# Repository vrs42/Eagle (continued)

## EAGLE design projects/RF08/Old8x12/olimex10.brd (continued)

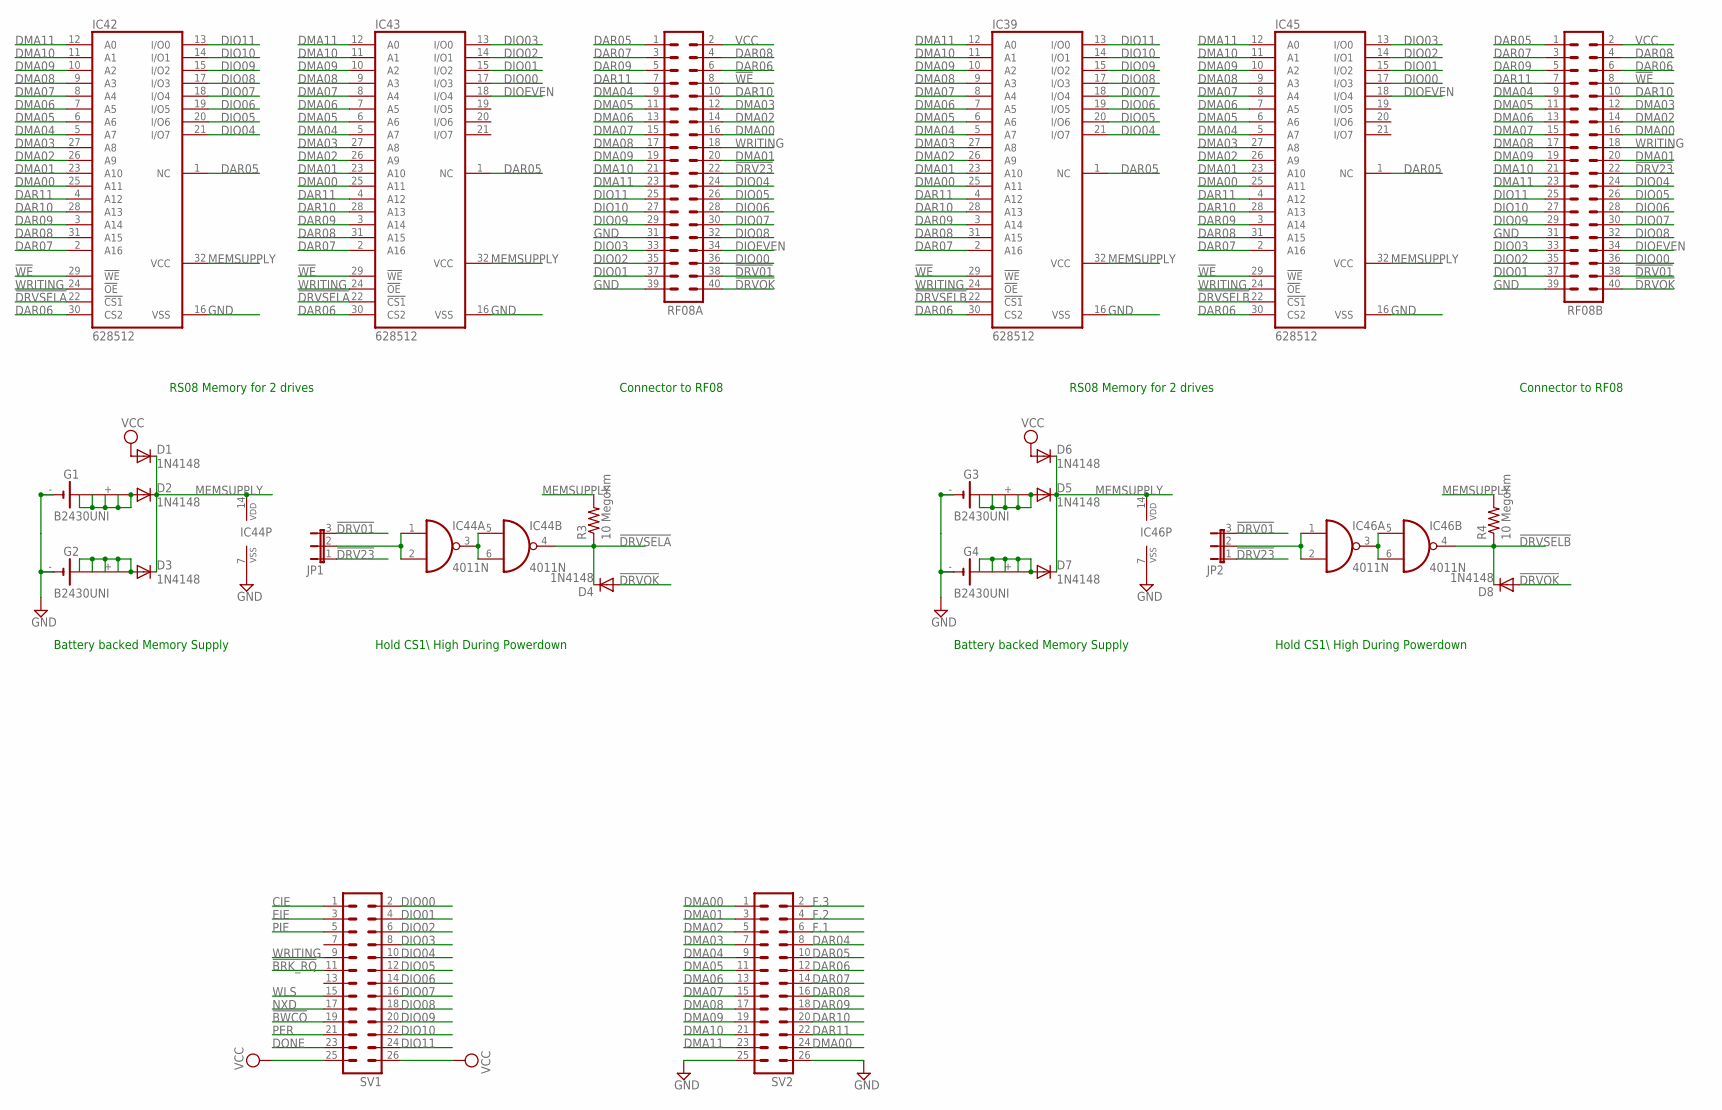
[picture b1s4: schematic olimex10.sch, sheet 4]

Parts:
D1, D2, D3, D4, D5, D6, D7, D8: 1N4148; DO35-10
G1, G2, G3, G4: B2430UNI
IC39, IC42, IC43, IC45: 628512; DIL32
IC44, IC46: 4011N; DIL14
JP1, JP2: JP2E; JP2
R3, R4: 10 Megohm; 0207/10
RF08A, RF08B: MA20-2
SV1, SV2: MA13-2

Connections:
!BRK_RQ: SV1.11; also elsewhere on the board
!BWCO: SV1.19; also elsewhere on the board
!DRV01: JP1.3, JP2.3, RF08A.38, RF08B.38; also elsewhere on the board
!DRV23: JP1.1, JP2.1, RF08A.22, RF08B.22; also elsewhere on the board
!DRVOK: D4.A, D8.A, RF08A.40, RF08B.40; also elsewhere on the board
!DRVSELA: D4.C, IC42.22 (!CS1), IC43.22 (!CS1), IC44.4 (O), R3.1
!DRVSELB: D8.C, IC39.22 (!CS1), IC45.22 (!CS1), IC46.4 (O), R4.1
!WE: IC39.29 (!WE), IC42.29 (!WE), IC43.29 (!WE), IC45.29 (!WE), RF08A.8, RF08B.8; also elsewhere on the board
CIE: SV1.1; also elsewhere on the board
DAR04: SV2.8; also elsewhere on the board
DAR05: IC39.1 (NC), IC42.1 (NC), IC43.1 (NC), IC45.1 (NC), RF08A.1, RF08B.1, SV2.10; also elsewhere on the board
DAR06: IC39.30 (CS2), IC42.30 (CS2), IC43.30 (CS2), IC45.30 (CS2), RF08A.6, RF08B.6, SV2.12; also elsewhere on the board
DAR07: IC39.2 (A16), IC42.2 (A16), IC43.2 (A16), IC45.2 (A16), RF08A.3, RF08B.3, SV2.14; also elsewhere on the board
DAR08: IC39.31 (A15), IC42.31 (A15), IC43.31 (A15), IC45.31 (A15), RF08A.4, RF08B.4, SV2.16; also elsewhere on the board
DAR09: IC39.3 (A14), IC42.3 (A14), IC43.3 (A14), IC45.3 (A14), RF08A.5, RF08B.5, SV2.18; also elsewhere on the board
DAR10: IC39.28 (A13), IC42.28 (A13), IC43.28 (A13), IC45.28 (A13), RF08A.10, RF08B.10, SV2.20; also elsewhere on the board
DAR11: IC39.4 (A12), IC42.4 (A12), IC43.4 (A12), IC45.4 (A12), RF08A.7, RF08B.7, SV2.22; also elsewhere on the board
DIO00: IC43.17 (I/O3), IC45.17 (I/O3), RF08A.36, RF08B.36, SV1.2; also elsewhere on the board
DIO01: IC43.15 (I/O2), IC45.15 (I/O2), RF08A.37, RF08B.37, SV1.4; also elsewhere on the board
DIO02: IC43.14 (I/O1), IC45.14 (I/O1), RF08A.35, RF08B.35, SV1.6; also elsewhere on the board
DIO03: IC43.13 (I/O0), IC45.13 (I/O0), RF08A.33, RF08B.33, SV1.8; also elsewhere on the board
DIO04: IC39.21 (I/O7), IC42.21 (I/O7), RF08A.24, RF08B.24, SV1.10; also elsewhere on the board
DIO05: IC39.20 (I/O6), IC42.20 (I/O6), RF08A.26, RF08B.26, SV1.12; also elsewhere on the board
DIO06: IC39.19 (I/O5), IC42.19 (I/O5), RF08A.28, RF08B.28, SV1.14; also elsewhere on the board
DIO07: IC39.18 (I/O4), IC42.18 (I/O4), RF08A.30, RF08B.30, SV1.16; also elsewhere on the board
DIO08: IC39.17 (I/O3), IC42.17 (I/O3), RF08A.32, RF08B.32, SV1.18; also elsewhere on the board
DIO09: IC39.15 (I/O2), IC42.15 (I/O2), RF08A.29, RF08B.29, SV1.20; also elsewhere on the board
DIO10: IC39.14 (I/O1), IC42.14 (I/O1), RF08A.27, RF08B.27, SV1.22; also elsewhere on the board
DIO11: IC39.13 (I/O0), IC42.13 (I/O0), RF08A.25, RF08B.25, SV1.24; also elsewhere on the board
DIOEVEN: IC43.18 (I/O4), IC45.18 (I/O4), RF08A.34, RF08B.34; also elsewhere on the board
DMA00: IC39.25 (A11), IC42.25 (A11), IC43.25 (A11), IC45.25 (A11), RF08A.16, RF08B.16, SV2.1, SV2.24; also elsewhere on the board
DMA01: IC39.23 (A10), IC42.23 (A10), IC43.23 (A10), IC45.23 (A10), RF08A.20, RF08B.20, SV2.3; also elsewhere on the board
DMA02: IC39.26 (A9), IC42.26 (A9), IC43.26 (A9), IC45.26 (A9), RF08A.14, RF08B.14, SV2.5; also elsewhere on the board
DMA03: IC39.27 (A8), IC42.27 (A8), IC43.27 (A8), IC45.27 (A8), RF08A.12, RF08B.12, SV2.7; also elsewhere on the board
DMA04: IC39.5 (A7), IC42.5 (A7), IC43.5 (A7), IC45.5 (A7), RF08A.9, RF08B.9, SV2.9; also elsewhere on the board
DMA05: IC39.6 (A6), IC42.6 (A6), IC43.6 (A6), IC45.6 (A6), RF08A.11, RF08B.11, SV2.11; also elsewhere on the board
DMA06: IC39.7 (A5), IC42.7 (A5), IC43.7 (A5), IC45.7 (A5), RF08A.13, RF08B.13, SV2.13; also elsewhere on the board
DMA07: IC39.8 (A4), IC42.8 (A4), IC43.8 (A4), IC45.8 (A4), RF08A.15, RF08B.15, SV2.15; also elsewhere on the board
DMA08: IC39.9 (A3), IC42.9 (A3), IC43.9 (A3), IC45.9 (A3), RF08A.17, RF08B.17, SV2.17; also elsewhere on the board
DMA09: IC39.10 (A2), IC42.10 (A2), IC43.10 (A2), IC45.10 (A2), RF08A.19, RF08B.19, SV2.19; also elsewhere on the board
DMA10: IC39.11 (A1), IC42.11 (A1), IC43.11 (A1), IC45.11 (A1), RF08A.21, RF08B.21, SV2.21; also elsewhere on the board
DMA11: IC39.12 (A0), IC42.12 (A0), IC43.12 (A0), IC45.12 (A0), RF08A.23, RF08B.23, SV2.23; also elsewhere on the board
DONE: SV1.23; also elsewhere on the board
EIE: SV1.3; also elsewhere on the board
F.1: SV2.6; also elsewhere on the board
F.2: SV2.4; also elsewhere on the board
F.3: SV2.2; also elsewhere on the board
GND: G1.-, G1.-@1 (-), G2.-, G2.-@1 (-), G3.-, G3.-@1 (-), G4.-, G4.-@1 (-), IC39.16 (VSS), IC42.16 (VSS), IC43.16 (VSS), IC44.7 (VSS), IC45.16 (VSS), IC46.7 (VSS), RF08A.31, RF08A.39, RF08B.31, RF08B.39, SV2.25, SV2.26; also elsewhere on the board
MEMSUPPLY: D1.C, D2.C, D3.C, D5.C, D6.C, D7.C, IC39.32 (VCC), IC42.32 (VCC), IC43.32 (VCC), IC44.14 (VDD), IC45.32 (VCC), IC46.14 (VDD), R3.2, R4.2
unnamed: IC44.3 (O), IC44.5 (I0), IC44.6 (I1)
unnamed: IC44.1 (I0), IC44.2 (I1), JP1.2
unnamed: D7.A, G4.+, G4.+@1 (+), G4.+@2 (+), G4.+@3 (+), G4.+@4 (+)
unnamed: IC46.3 (O), IC46.5 (I0), IC46.6 (I1)
unnamed: IC46.1 (I0), IC46.2 (I1), JP2.2
unnamed: D5.A, G3.+, G3.+@1 (+), G3.+@2 (+), G3.+@3 (+), G3.+@4 (+)
unnamed: D3.A, G2.+, G2.+@1 (+), G2.+@2 (+), G2.+@3 (+), G2.+@4 (+)
unnamed: D2.A, G1.+, G1.+@1 (+), G1.+@2 (+), G1.+@3 (+), G1.+@4 (+)
NXD: SV1.17; also elsewhere on the board
PER: SV1.21; also elsewhere on the board
PIE: SV1.5; also elsewhere on the board
VCC: D1.A, D6.A, RF08A.2, RF08B.2, SV1.25, SV1.26; also elsewhere on the board
WLS: SV1.15; also elsewhere on the board
WRITING: IC39.24 (!OE), IC42.24 (!OE), IC43.24 (!OE), IC45.24 (!OE), RF08A.18, RF08B.18, SV1.9; also elsewhere on the board

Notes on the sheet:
Hold CS1\\ High During Powerdown
Battery backed Memory Supply
RS08 Memory for 2 drives
Connector to RF08

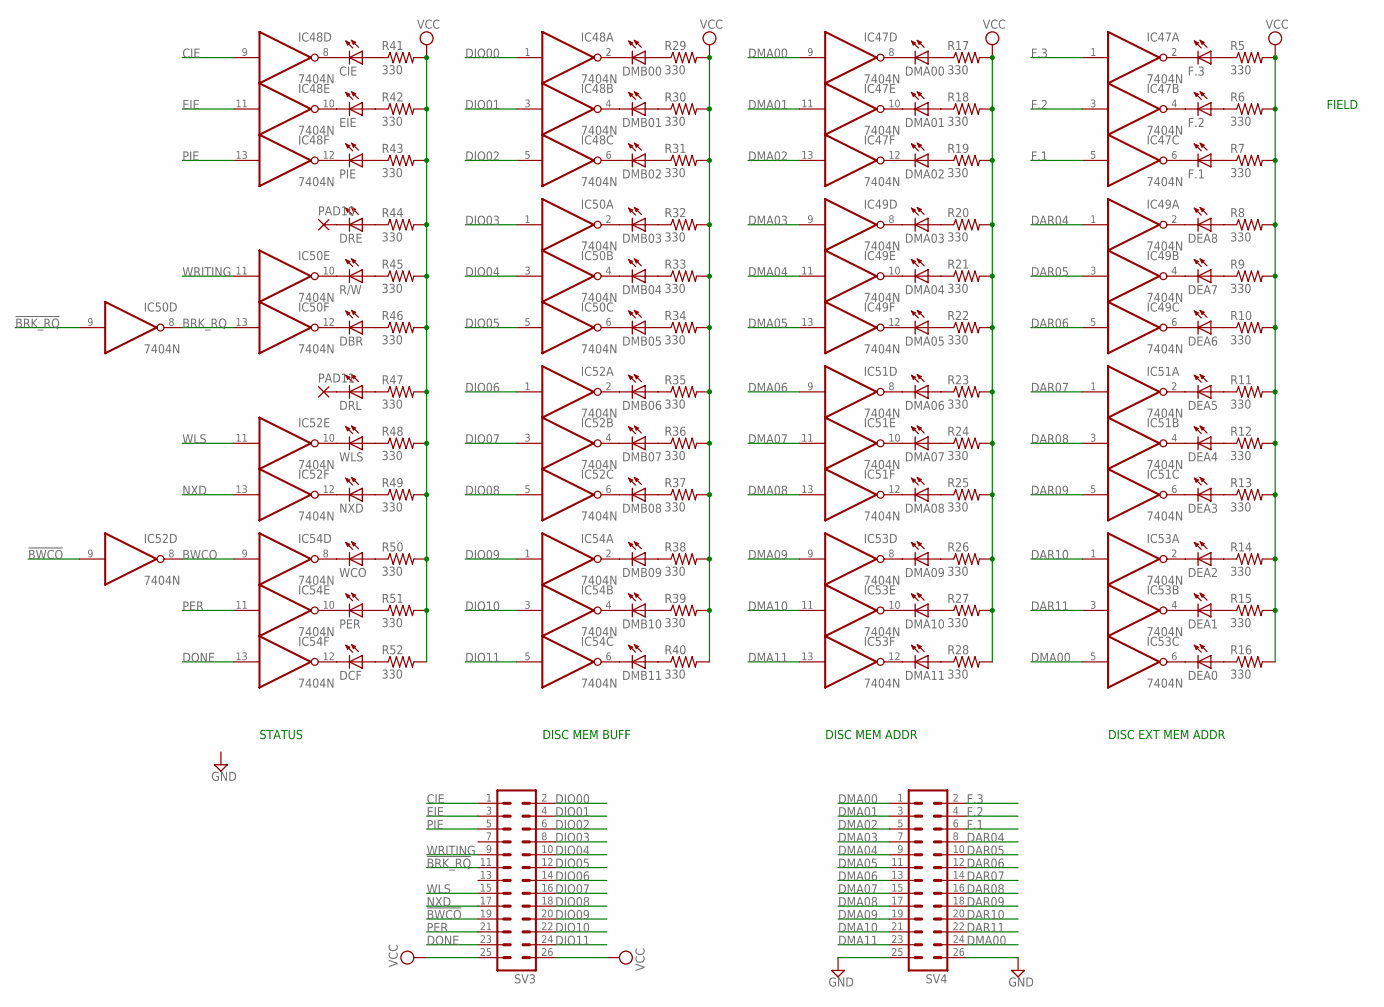
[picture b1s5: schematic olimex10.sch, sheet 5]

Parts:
CIE: LED5MM
DBR: LED5MM
DCF: LED5MM
DEA0, DEA1, DEA2, DEA3, DEA4, DEA5, DEA6, DEA7, DEA8: LED5MM
DMA00, DMA01, DMA02, DMA03, DMA04, DMA05, DMA06, DMA07, DMA08, DMA09, DMA10, DMA11: LED5MM
DMB00, DMB01, DMB02, DMB03, DMB04, DMB05, DMB06, DMB07, DMB08, DMB09, DMB10, DMB11: LED5MM
DRE: LED5MM
DRL: LED5MM
EIE: LED5MM
F.1, F.2, F.3: LED5MM
IC47, IC48, IC49, IC50, IC51, IC52, IC53, IC54: 7404N; DIL14
NXD: LED5MM
PAD10, PAD11: 1,6/0,8
PER: LED5MM
PIE: LED5MM
R5, R6, R7, R8, R9, R10, R11, R12, R13, R14, R15, R16, R17, R18, R19, R20, R21, R22, R23, R24, R25, R26, R27, R28, R29, R30, R31, R32, R33, R34, R35, R36, R37, R38, R39, R40, R41, R42, R43, R44, R45, R46, R47, R48, R49, R50, R51, R52: 330; 0207/10
R/W: LED5MM
SV3, SV4: MA13-2
WCO: LED5MM
WLS: LED5MM

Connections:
!BRK_RQ: IC50.9 (I), SV3.11; also elsewhere on the board
!BWCO: IC52.9 (I), SV3.19; also elsewhere on the board
BRK_RQ: IC50.8 (O), IC50.13 (I)
BWCO: IC52.8 (O), IC54.9 (I)
CIE: IC48.9 (I), SV3.1; also elsewhere on the board
DAR04: IC49.1 (I), SV4.8; also elsewhere on the board
DAR05: IC49.3 (I), SV4.10; also elsewhere on the board
DAR06: IC49.5 (I), SV4.12; also elsewhere on the board
DAR07: IC51.1 (I), SV4.14; also elsewhere on the board
DAR08: IC51.3 (I), SV4.16; also elsewhere on the board
DAR09: IC51.5 (I), SV4.18; also elsewhere on the board
DAR10: IC53.1 (I), SV4.20; also elsewhere on the board
DAR11: IC53.3 (I), SV4.22; also elsewhere on the board
DIO00: IC48.1 (I), SV3.2; also elsewhere on the board
DIO01: IC48.3 (I), SV3.4; also elsewhere on the board
DIO02: IC48.5 (I), SV3.6; also elsewhere on the board
DIO03: IC50.1 (I), SV3.8; also elsewhere on the board
DIO04: IC50.3 (I), SV3.10; also elsewhere on the board
DIO05: IC50.5 (I), SV3.12; also elsewhere on the board
DIO06: IC52.1 (I), SV3.14; also elsewhere on the board
DIO07: IC52.3 (I), SV3.16; also elsewhere on the board
DIO08: IC52.5 (I), SV3.18; also elsewhere on the board
DIO09: IC54.1 (I), SV3.20; also elsewhere on the board
DIO10: IC54.3 (I), SV3.22; also elsewhere on the board
DIO11: IC54.5 (I), SV3.24; also elsewhere on the board
DMA00: IC47.9 (I), IC53.5 (I), SV4.1, SV4.24; also elsewhere on the board
DMA01: IC47.11 (I), SV4.3; also elsewhere on the board
DMA02: IC47.13 (I), SV4.5; also elsewhere on the board
DMA03: IC49.9 (I), SV4.7; also elsewhere on the board
DMA04: IC49.11 (I), SV4.9; also elsewhere on the board
DMA05: IC49.13 (I), SV4.11; also elsewhere on the board
DMA06: IC51.9 (I), SV4.13; also elsewhere on the board
DMA07: IC51.11 (I), SV4.15; also elsewhere on the board
DMA08: IC51.13 (I), SV4.17; also elsewhere on the board
DMA09: IC53.9 (I), SV4.19; also elsewhere on the board
DMA10: IC53.11 (I), SV4.21; also elsewhere on the board
DMA11: IC53.13 (I), SV4.23; also elsewhere on the board
DONE: IC54.13 (I), SV3.23; also elsewhere on the board
EIE: IC48.11 (I), SV3.3; also elsewhere on the board
F.1: IC47.5 (I), SV4.6; also elsewhere on the board
F.2: IC47.3 (I), SV4.4; also elsewhere on the board
F.3: IC47.1 (I), SV4.2; also elsewhere on the board
GND: IC47.7 (GND), IC48.7 (GND), IC49.7 (GND), IC50.7 (GND), IC51.7 (GND), IC52.7 (GND), IC53.7 (GND), IC54.7 (GND), SV4.25, SV4.26; also elsewhere on the board
unnamed: F.3.A, R5.1
unnamed: F.2.A, R6.1
unnamed: F.1.A, R7.1
unnamed: DEA8.A, R8.1
unnamed: DEA7.A, R9.1
unnamed: DEA6.A, R10.1
unnamed: DEA5.A, R11.1
unnamed: DEA4.A, R12.1
unnamed: DEA3.A, R13.1
unnamed: DEA2.A, R14.1
unnamed: DEA1.A, R15.1
unnamed: DEA0.A, R16.1
unnamed: DMA00.A, R17.1
unnamed: DMA01.A, R18.1
unnamed: DMA02.A, R19.1
unnamed: DMA03.A, R20.1
unnamed: DMA04.A, R21.1
unnamed: DMA05.A, R22.1
unnamed: DMA06.A, R23.1
unnamed: DMA07.A, R24.1
unnamed: DMA08.A, R25.1
unnamed: DMA09.A, R26.1
unnamed: DMA10.A, R27.1
unnamed: DMA11.A, R28.1
unnamed: DMB00.A, R29.1
unnamed: DMB01.A, R30.1
unnamed: DMB02.A, R31.1
unnamed: DMB03.A, R32.1
unnamed: DMB04.A, R33.1
unnamed: DMB05.A, R34.1
unnamed: DMB06.A, R35.1
unnamed: DMB07.A, R36.1
unnamed: DMB08.A, R37.1
unnamed: DMB09.A, R38.1
unnamed: DMB10.A, R39.1
unnamed: DMB11.A, R40.1
unnamed: CIE.A, R41.1
unnamed: EIE.A, R42.1
unnamed: PIE.A, R43.1
unnamed: DRE.A, R44.1
unnamed: R45.1, R/W.A
unnamed: DBR.A, R46.1
unnamed: DRL.A, R47.1
unnamed: R48.1, WLS.A
unnamed: NXD.A, R49.1
unnamed: R50.1, WCO.A
unnamed: PER.A, R51.1
unnamed: DCF.A, R52.1
unnamed: F.3.K (C), IC47.2 (O)
unnamed: F.2.K (C), IC47.4 (O)
unnamed: F.1.K (C), IC47.6 (O)
unnamed: DMA00.K (C), IC47.8 (O)
unnamed: DMA01.K (C), IC47.10 (O)
unnamed: DMA02.K (C), IC47.12 (O)
unnamed: DMB00.K (C), IC48.2 (O)
unnamed: DMB01.K (C), IC48.4 (O)
unnamed: DMB02.K (C), IC48.6 (O)
unnamed: CIE.K (C), IC48.8 (O)
unnamed: EIE.K (C), IC48.10 (O)
unnamed: IC48.12 (O), PIE.K (C)
unnamed: DEA7.K (C), IC49.4 (O)
unnamed: DEA6.K (C), IC49.6 (O)
unnamed: DMA03.K (C), IC49.8 (O)
unnamed: DMA04.K (C), IC49.10 (O)
unnamed: DMA05.K (C), IC49.12 (O)
unnamed: DMB03.K (C), IC50.2 (O)
unnamed: DMB04.K (C), IC50.4 (O)
unnamed: DMB05.K (C), IC50.6 (O)
unnamed: IC50.10 (O), R/W.K (C)
unnamed: DBR.K (C), IC50.12 (O)
unnamed: DEA5.K (C), IC51.2 (O)
unnamed: DEA4.K (C), IC51.4 (O)
unnamed: DEA3.K (C), IC51.6 (O)
unnamed: DMA06.K (C), IC51.8 (O)
unnamed: DMA07.K (C), IC51.10 (O)
unnamed: DMA08.K (C), IC51.12 (O)
unnamed: DMB06.K (C), IC52.2 (O)
unnamed: DMB07.K (C), IC52.4 (O)
unnamed: DMB08.K (C), IC52.6 (O)
unnamed: IC52.10 (O), WLS.K (C)
unnamed: IC52.12 (O), NXD.K (C)
unnamed: DEA2.K (C), IC53.2 (O)
unnamed: DEA1.K (C), IC53.4 (O)
unnamed: DEA0.K (C), IC53.6 (O)
unnamed: DMA09.K (C), IC53.8 (O)
unnamed: DMA10.K (C), IC53.10 (O)
unnamed: DMA11.K (C), IC53.12 (O)
unnamed: DMB09.K (C), IC54.2 (O)
unnamed: DMB10.K (C), IC54.4 (O)
unnamed: DMB11.K (C), IC54.6 (O)
unnamed: IC54.8 (O), WCO.K (C)
unnamed: IC54.10 (O), PER.K (C)
unnamed: DCF.K (C), IC54.12 (O)
unnamed: DRE.K (C), PAD10.1
unnamed: DRL.K (C), PAD11.1
unnamed: DEA8.K (C), IC49.2 (O)
NXD: IC52.13 (I), SV3.17; also elsewhere on the board
PER: IC54.11 (I), SV3.21; also elsewhere on the board
PIE: IC48.13 (I), SV3.5; also elsewhere on the board
VCC: IC47.14 (VCC), IC48.14 (VCC), IC49.14 (VCC), IC50.14 (VCC), IC51.14 (VCC), IC52.14 (VCC), IC53.14 (VCC), IC54.14 (VCC), R5.2, R6.2, R7.2, R8.2, R9.2, R10.2, R11.2, R12.2, R13.2, R14.2, R15.2, R16.2, R17.2, R18.2, R19.2, R20.2, R21.2, R22.2, R23.2, R24.2, R25.2, R26.2, R27.2, R28.2, R29.2, R30.2, R31.2, R32.2, R33.2, R34.2, R35.2, R36.2, R37.2, R38.2, R39.2, R40.2, R41.2, R42.2, R43.2, R44.2, R45.2, R46.2, R47.2, R48.2, R49.2, R50.2, R51.2, R52.2, SV3.25, SV3.26; also elsewhere on the board
WLS: IC52.11 (I), SV3.15; also elsewhere on the board
WRITING: IC50.11 (I), SV3.9; also elsewhere on the board

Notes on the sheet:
FIELD
DISC EXT MEM ADDR
DISC MEM ADDR
DISC MEM BUFF
STATUS

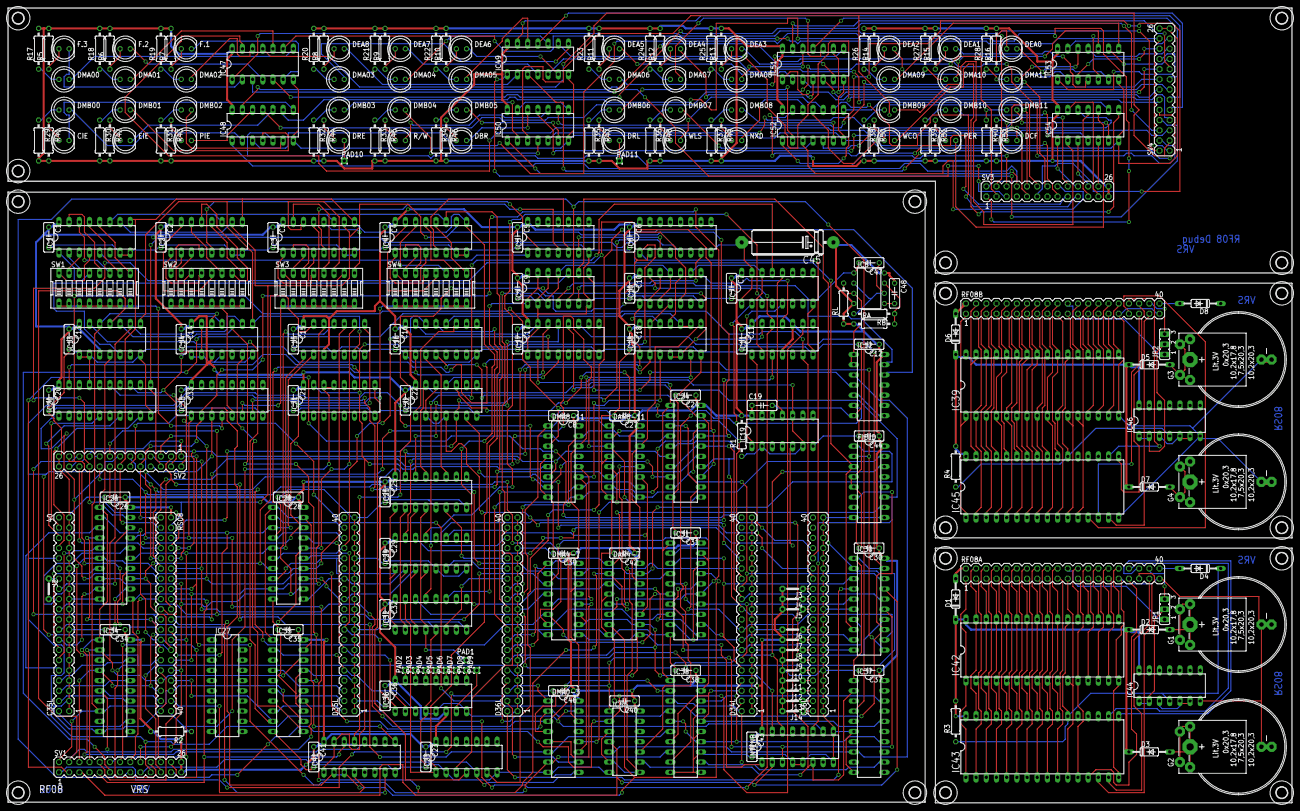
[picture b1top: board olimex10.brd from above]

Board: 2 copper layers, 320.0 x 198.1 mm, 283 parts (0 on the bottom side), 335 nets.

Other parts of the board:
U$1, U$2, U$3, U$4, U$5, U$6, U$7, U$8, U$9, U$10, U$11, U$12, U$13, U$14, U$15, U$16, U$17: 2,8

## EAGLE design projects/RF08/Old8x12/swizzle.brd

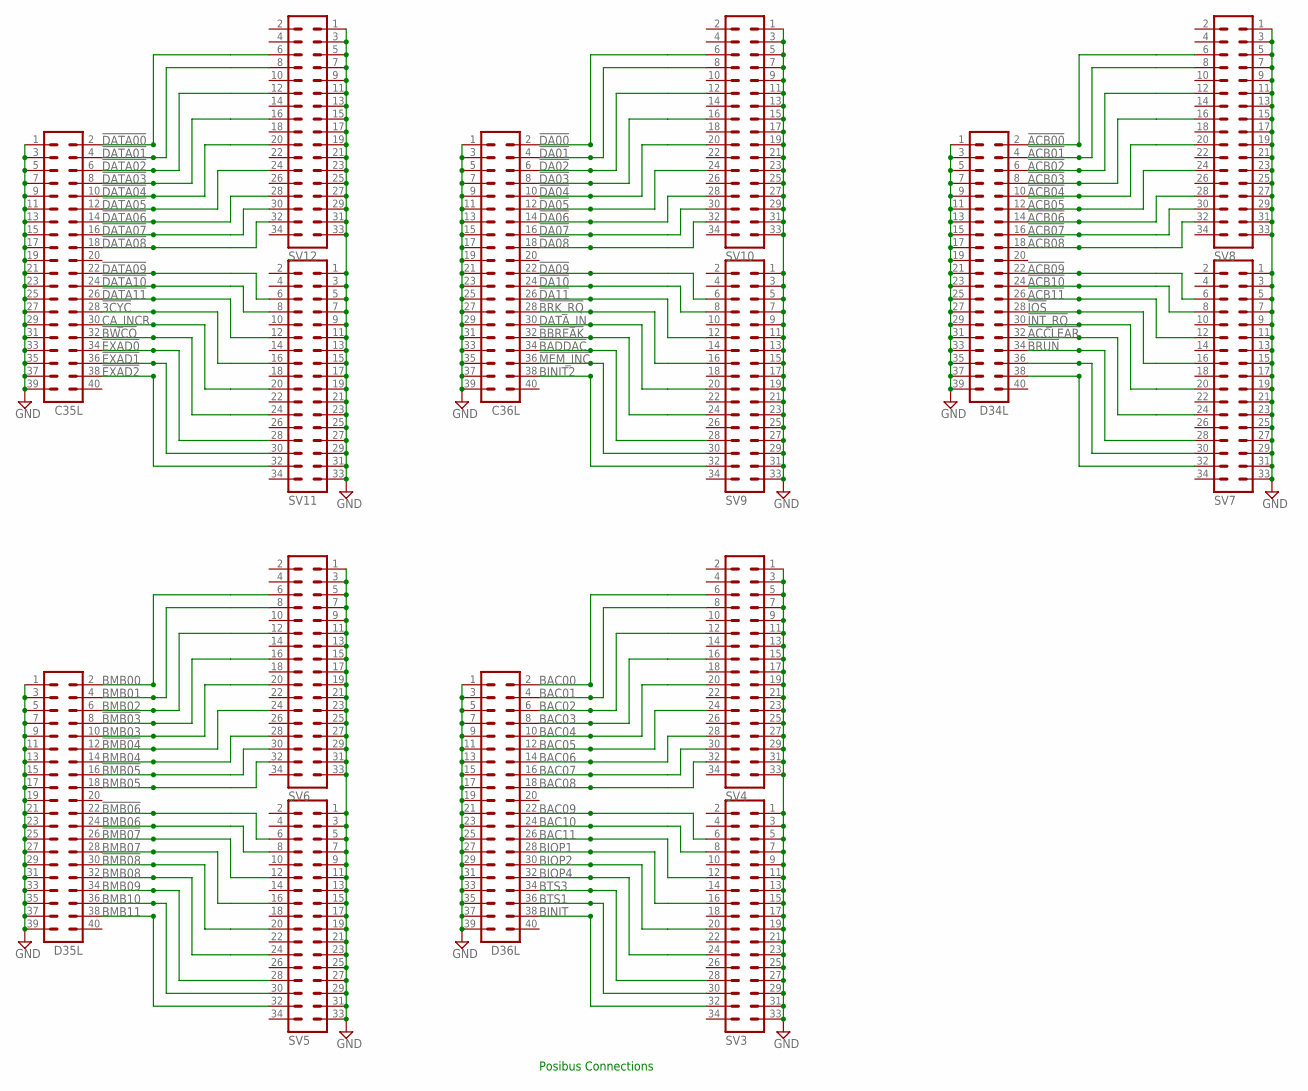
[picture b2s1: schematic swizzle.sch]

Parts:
C35L, C36L: MA20-2
D34L, D35L, D36L: MA20-2
SV3, SV4, SV5, SV6, SV7, SV8, SV9, SV10, SV11, SV12: MA17-2

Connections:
!3CYC: C35L.28, SV11.16
!ACB00: D34L.2, SV8.6
!ACB01: D34L.4, SV8.8
!ACB02: D34L.6, SV8.12
!ACB03: D34L.8, SV8.16
!ACB04: D34L.10, SV8.20
!ACB05: D34L.12, SV8.24
!ACB06: D34L.14, SV8.28
!ACB07: D34L.16, SV8.30
!ACB08: D34L.18, SV8.32
!ACB09: D34L.22, SV7.6
!ACB10: D34L.24, SV7.8
!ACB11: D34L.26, SV7.12
!ACCLEAR: D34L.32, SV7.24
!BADDAC: C36L.34, SV9.28
!BBREAK: C36L.32, SV9.24
!BMB03: D35L.8, SV6.16
!BMB04: D35L.12, SV6.24
!BMB05: D35L.16, SV6.30
!BMB06: D35L.22, SV5.6
!BMB07: D35L.26, SV5.12
!BMB08: D35L.30, SV5.20
!BRK_RQ: C36L.28, SV9.16
!BRUN: D34L.34, SV7.28
!BWCO: C35L.32, SV11.24
!DA00: C36L.2, SV10.6
!DA01: C36L.4, SV10.8
!DA02: C36L.6, SV10.12
!DA03: C36L.8, SV10.16
!DA04: C36L.10, SV10.20
!DA05: C36L.12, SV10.24
!DA06: C36L.14, SV10.28
!DA07: C36L.16, SV10.30
!DA08: C36L.18, SV10.32
!DA09: C36L.22, SV9.6
!DA10: C36L.24, SV9.8
!DA11: C36L.26, SV9.12
!DATA00: C35L.2, SV12.6
!DATA01: C35L.4, SV12.8
!DATA02: C35L.6, SV12.12
!DATA03: C35L.8, SV12.16
!DATA04: C35L.10, SV12.20
!DATA05: C35L.12, SV12.24
!DATA06: C35L.14, SV12.28
!DATA07: C35L.16, SV12.30
!DATA08: C35L.18, SV12.32
!DATA09: C35L.22, SV11.6
!DATA10: C35L.24, SV11.8
!DATA11: C35L.26, SV11.12
!EXAD0: C35L.34, SV11.28
!EXAD1: C35L.36, SV11.30
!EXAD2: C35L.38, SV11.32
!INT_RQ: D34L.30, SV7.20
!IOS: D34L.28, SV7.16
!MEM_INC: C36L.36, SV9.30
BAC00: D36L.2, SV4.6
BAC01: D36L.4, SV4.8
BAC02: D36L.6, SV4.12
BAC03: D36L.8, SV4.16
BAC04: D36L.10, SV4.20
BAC05: D36L.12, SV4.24
BAC06: D36L.14, SV4.28
BAC07: D36L.16, SV4.30
BAC08: D36L.18, SV4.32
BAC09: D36L.22, SV3.6
BAC10: D36L.24, SV3.8
BAC11: D36L.26, SV3.12
BINIT: D36L.38, SV3.32
BINIT2: C36L.38, SV9.32
BIOP1: D36L.28, SV3.16
BIOP2: D36L.30, SV3.20
BIOP4: D36L.32, SV3.24
BMB00: D35L.2, SV6.6
BMB01: D35L.4, SV6.8
BMB02: D35L.6, SV6.12
BMB03: D35L.10, SV6.20
BMB04: D35L.14, SV6.28
BMB05: D35L.18, SV6.32
BMB06: D35L.24, SV5.8
BMB07: D35L.28, SV5.16
BMB08: D35L.32, SV5.24
BMB09: D35L.34, SV5.28
BMB10: D35L.36, SV5.30
BMB11: D35L.38, SV5.32
BTS1: D36L.36, SV3.30
BTS3: D36L.34, SV3.28
CA_INCR: C35L.30, SV11.20
DATA_IN: C36L.30, SV9.20
GND: C35L.1, C35L.3, C35L.5, C35L.7, C35L.9, C35L.11, C35L.13, C35L.15, C35L.17, C35L.19, C35L.21, C35L.23, C35L.25, C35L.27, C35L.29, C35L.31, C35L.33, C35L.35, C35L.37, C35L.39, C36L.1, C36L.3, C36L.5, C36L.7, C36L.9, C36L.11, C36L.13, C36L.15, C36L.17, C36L.19, C36L.21, C36L.23, C36L.25, C36L.27, C36L.29, C36L.31, C36L.33, C36L.35, C36L.37, C36L.39, D34L.1, D34L.3, D34L.5, D34L.7, D34L.9, D34L.11, D34L.13, D34L.15, D34L.17, D34L.19, D34L.21, D34L.23, D34L.25, D34L.27, D34L.29, D34L.31, D34L.33, D34L.35, D34L.37, D34L.39, D35L.1, D35L.3, D35L.5, D35L.7, D35L.9, D35L.11, D35L.13, D35L.15, D35L.17, D35L.19, D35L.21, D35L.23, D35L.25, D35L.27, D35L.29, D35L.31, D35L.33, D35L.35, D35L.37, D35L.39, D36L.1, D36L.3, D36L.5, D36L.7, D36L.9, D36L.11, D36L.13, D36L.15, D36L.17, D36L.19, D36L.21, D36L.23, D36L.25, D36L.27, D36L.29, D36L.31, D36L.33, D36L.35, D36L.37, D36L.39, SV3.1, SV3.3, SV3.5, SV3.7, SV3.9, SV3.11, SV3.13, SV3.15, SV3.17, SV3.19, SV3.21, SV3.23, SV3.25, SV3.27, SV3.29, SV3.31, SV3.33, SV4.1, SV4.3, SV4.5, SV4.7, SV4.9, SV4.11, SV4.13, SV4.15, SV4.17, SV4.19, SV4.21, SV4.23, SV4.25, SV4.27, SV4.29, SV4.31, SV4.33, SV5.1, SV5.3, SV5.5, SV5.7, SV5.9, SV5.11, SV5.13, SV5.15, SV5.17, SV5.19, SV5.21, SV5.23, SV5.25, SV5.27, SV5.29, SV5.31, SV5.33, SV6.1, SV6.3, SV6.5, SV6.7, SV6.9, SV6.11, SV6.13, SV6.15, SV6.17, SV6.19, SV6.21, SV6.23, SV6.25, SV6.27, SV6.29, SV6.31, SV6.33, SV7.1, SV7.3, SV7.5, SV7.7, SV7.9, SV7.11, SV7.13, SV7.15, SV7.17, SV7.19, SV7.21, SV7.23, SV7.25, SV7.27, SV7.29, SV7.31, SV7.33, SV8.1, SV8.3, SV8.5, SV8.7, SV8.9, SV8.11, SV8.13, SV8.15, SV8.17, SV8.19, SV8.21, SV8.23, SV8.25, SV8.27, SV8.29, SV8.31, SV8.33, SV9.1, SV9.3, SV9.5, SV9.7, SV9.9, SV9.11, SV9.13, SV9.15, SV9.17, SV9.19, SV9.21, SV9.23, SV9.25, SV9.27, SV9.29, SV9.31, SV9.33, SV10.1, SV10.3, SV10.5, SV10.7, SV10.9, SV10.11, SV10.13, SV10.15, SV10.17, SV10.19, SV10.21, SV10.23, SV10.25, SV10.27, SV10.29, SV10.31, SV10.33, SV11.1, SV11.3, SV11.5, SV11.7, SV11.9, SV11.11, SV11.13, SV11.15, SV11.17, SV11.19, SV11.21, SV11.23, SV11.25, SV11.27, SV11.29, SV11.31, SV11.33, SV12.1, SV12.3, SV12.5, SV12.7, SV12.9, SV12.11, SV12.13, SV12.15, SV12.17, SV12.19, SV12.21, SV12.23, SV12.25, SV12.27, SV12.29, SV12.31, SV12.33
unnamed: D34L.36, SV7.30
unnamed: D34L.38, SV7.32

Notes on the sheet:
Posibus Connections

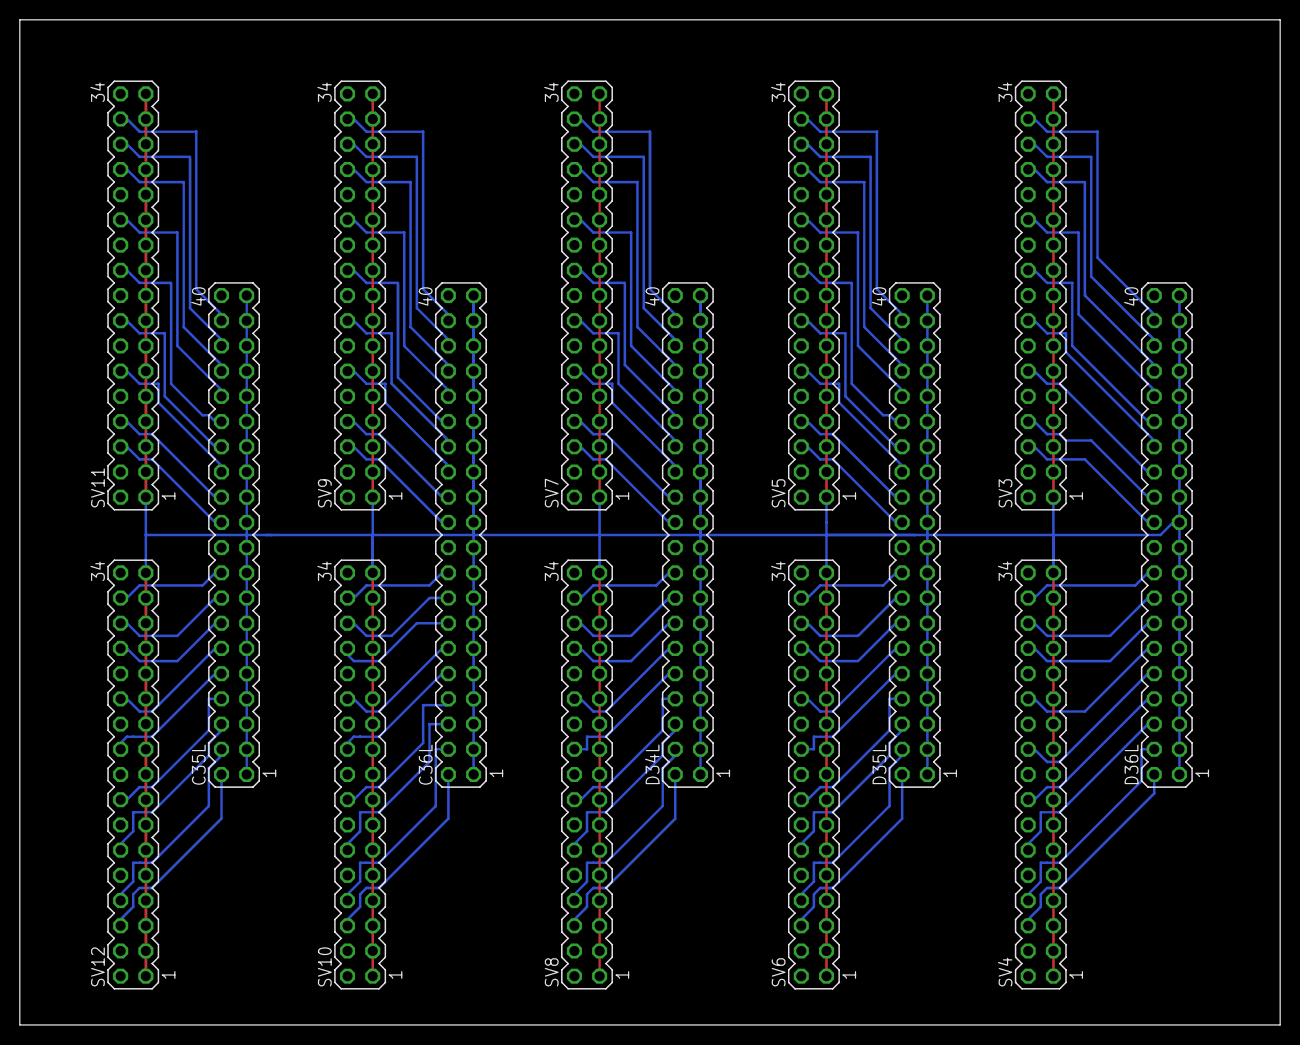
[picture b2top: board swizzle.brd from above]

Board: 2 copper layers, 127.0 x 101.3 mm, 15 parts (0 on the bottom side), 91 nets.

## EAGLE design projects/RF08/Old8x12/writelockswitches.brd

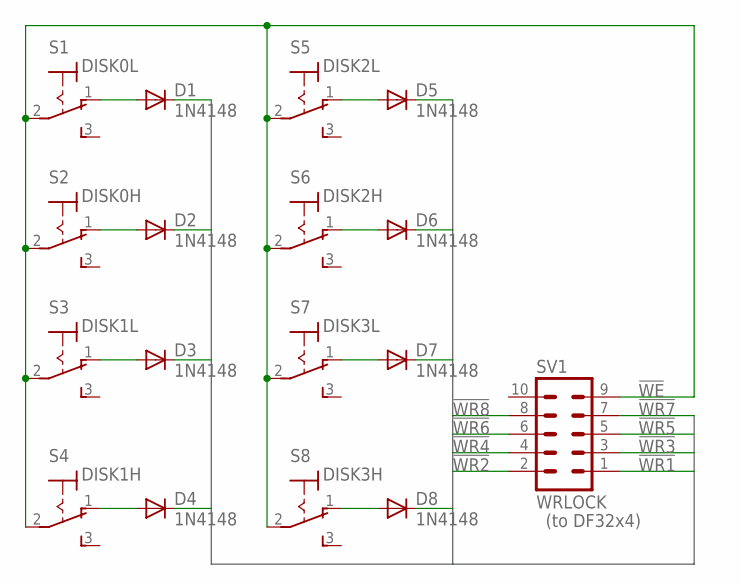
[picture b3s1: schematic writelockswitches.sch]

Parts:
D1, D2, D3, D4, D5, D6, D7, D8: 1N4148; DO35-10
S1: DISK0L; 320-916
S2: DISK0H; 320-916
S3: DISK1L; 320-916
S4: DISK1H; 320-916
S5: DISK2L; 320-916
S6: DISK2H; 320-916
S7: DISK3L; 320-916
S8: DISK3H; 320-916
SV1: WRLOCK; MA05-2

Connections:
!WE: S1.2, S2.2, S3.2, S4.2, S5.2, S6.2, S7.2, S8.2, SV1.9
!WR1: D1.C, SV1.1
!WR2: D2.C, SV1.2
!WR3: D3.C, SV1.3
!WR4: D4.C, SV1.4
!WR5: D5.C, SV1.5
!WR6: D6.C, SV1.6
!WR7: D7.C, SV1.7
!WR8: D8.C, SV1.8
unnamed: D1.A, S1.1 (O)
unnamed: D2.A, S2.1 (O)
unnamed: D3.A, S3.1 (O)
unnamed: D4.A, S4.1 (O)
unnamed: D5.A, S5.1 (O)
unnamed: D6.A, S6.1 (O)
unnamed: D7.A, S7.1 (O)
unnamed: D8.A, S8.1 (O)

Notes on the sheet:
(to DF32x4)

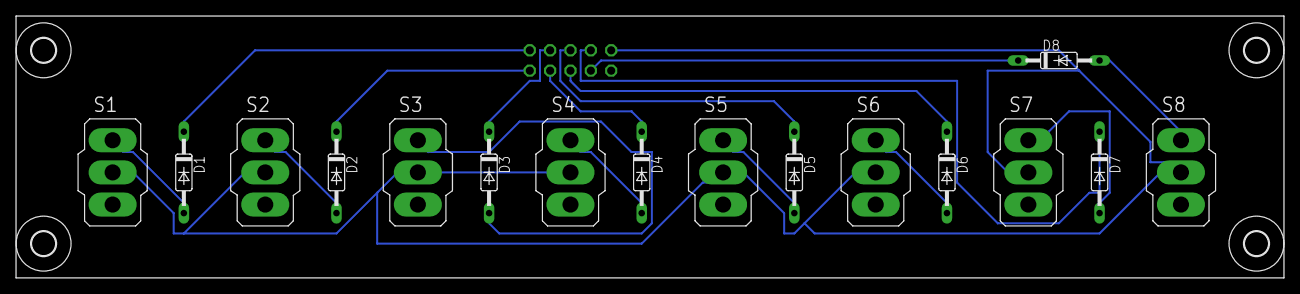
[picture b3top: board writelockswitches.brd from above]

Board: 2 copper layers, 158.3 x 32.7 mm, 21 parts (1 on the bottom side), 17 nets.

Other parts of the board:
U$1, U$2, U$3, U$4: 3,0
